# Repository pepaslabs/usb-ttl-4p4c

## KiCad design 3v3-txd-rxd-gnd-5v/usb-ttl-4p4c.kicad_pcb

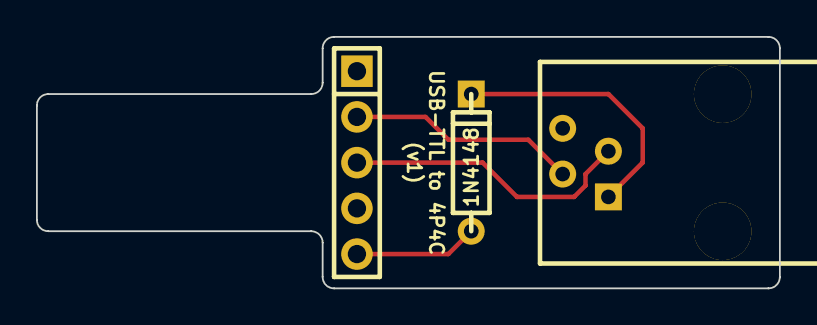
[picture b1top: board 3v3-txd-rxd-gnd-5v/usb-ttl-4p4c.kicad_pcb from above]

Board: 4 copper layers, 41.3 x 14.0 mm, 3 parts (0 on the bottom side), 5 nets.

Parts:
D1: 1N4148; DIODE_SS_059A_03_PL
J1: 4P4C; A-2004-3-4-LP-N-R_059A
P1: CONN_5X1; SIL-5

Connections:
5V: D1.1, P1.5
GND: J1.4, P1.4
unnamed: D1.2, J1.1
RXD: J1.3, P1.3
TXD: J1.2, P1.2

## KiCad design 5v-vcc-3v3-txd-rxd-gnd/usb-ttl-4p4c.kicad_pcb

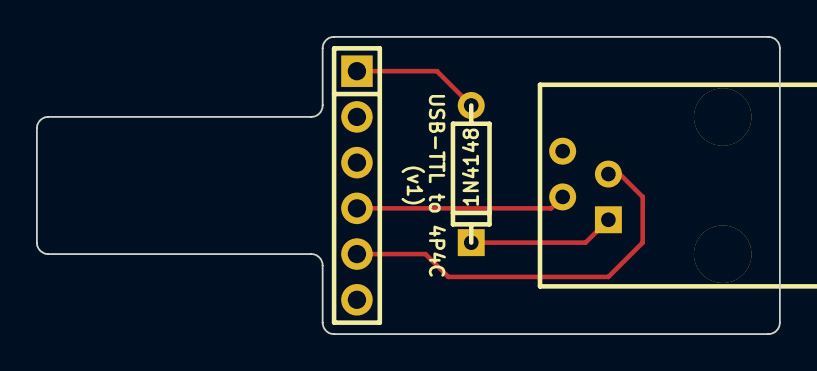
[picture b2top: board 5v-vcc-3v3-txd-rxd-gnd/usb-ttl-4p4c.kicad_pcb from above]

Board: 4 copper layers, 41.3 x 16.5 mm, 3 parts (0 on the bottom side), 5 nets.

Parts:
D1: 1N4148; DIODE_SS_059A_03_PL
J1: 4P4C; A-2004-3-4-LP-N-R_059A
P1: CONN_6X1; SIL-6

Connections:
5V: D1.1, P1.1
GND: J1.4, P1.6
unnamed: D1.2, J1.1
RXD: J1.3, P1.5
TXD: J1.2, P1.4

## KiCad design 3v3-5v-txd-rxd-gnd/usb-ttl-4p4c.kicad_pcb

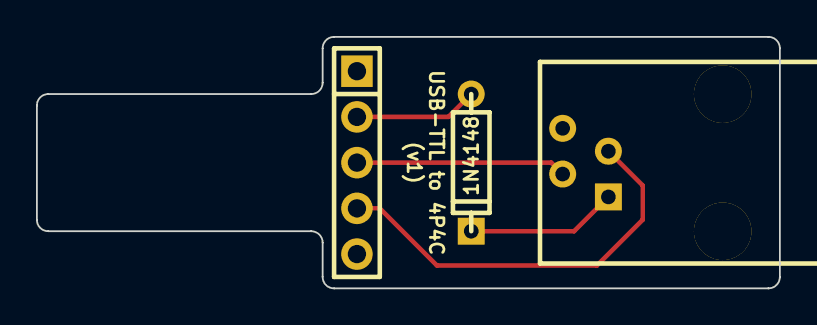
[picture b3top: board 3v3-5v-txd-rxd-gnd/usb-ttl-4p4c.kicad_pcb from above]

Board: 4 copper layers, 41.3 x 14.0 mm, 3 parts (0 on the bottom side), 5 nets.

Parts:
D1: 1N4148; DIODE_SS_059A_03_PL
J1: 4P4C; A-2004-3-4-LP-N-R_059A
P1: CONN_5X1; SIL-5

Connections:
5V: D1.1, P1.2
GND: J1.4, P1.5
unnamed: D1.2, J1.1
RXD: J1.3, P1.4
TXD: J1.2, P1.3

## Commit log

2018-04-04 alternate pinout
2018-04-04 ch340g
2018-04-05 adding a diode
